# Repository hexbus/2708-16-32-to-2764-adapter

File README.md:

# 2708 / 2716 / 2732 to 2764 adapter

A **28 × 38.5 mm** read-only adapter for Intel-pinout 2708, 2716 and 2732 sockets. It takes a 5 V DIP-28 2764/27C64 EPROM or Microchip AT28C64B EEPROM. The three host shunts sit beside the memory and remain accessible with it installed. The notched top outline marks all 28 memory pads.

Program the replacement chip separately. Place the original image at offset **0x0000** in the 8 KiB image for the replacement. The rest can be filled with `FF`.

Check the host's +5 V current budget, especially in a 2708 socket. The Intel 2708 datasheet specifies up to 10 mA from +5 V. An Intel NMOS 2764 can draw up to 105 mA from that rail with VPP tied to VCC. Allow for the replacement's specified read current and the adapter's pull-up. [Intel 2708 DC characteristics](https://deramp.com/downloads/mfe_archive/050-Component%20Specifications/Intel/Memory%20Components/Intel%202708.pdf) · [Intel 2764 DC characteristics](https://deramp.com/downloads/mfe_archive/050-Component%20Specifications/Intel/Memory%20Components/Intel%202764.pdf)

| Host socket | JP1 CE | JP2 A10 | JP3 A11 | Bytes visible |
| --- | --- | --- | --- | --- |
| 2708 | 1–2 | 1–2 | 1–2 | `0000–03FF` (1 KiB) |
| 2716 | 2–3 | 2–3 | 1–2 | `0000–07FF` (2 KiB) |
| 2732 / 2732A | 2–3 | 2–3 | 2–3 | `0000–0FFF` (4 KiB) |

On the top, with the EPROM notch up, the shunts are labeled CE, A10 and A11 from top to bottom. The square pad on each is pin 1, nearest the notch end. Use one shunt per header. Set the shunts with power off and verify the host socket pinout before inserting the adapter. The three-supply TI TMS2716 and the TMS2532 have different pinouts.

Each host shunt header has its own outline on the top. Read the underside chart with its notch marker up. **↑** means place the shunt toward the notch (pins 1–2). **↓** means place it away from the notch (pins 2–3).

Bridge **JP4** for a 2764/27C64 that requires +5 V on VPP during reads. Leave it open for the AT28C64B, which has NC on pin 1. The socket is for normal reads only. Programming voltages on the host's control pins are outside the design limits.

## Wiring

| Signal | 24-pin host J1 | 28-pin memory U1 |
| --- | --- | --- |
| A7 through A0 | 1–8 | 3–10 |
| D0 through D2 | 9–11 | 11–13 |
| GND | 12 | 14 and A12 on pin 2 |
| D3 through D7 | 13–17 | 15–19 |
| /CE | 20 in 2708 mode, 18 otherwise | 20, with a 10 kΩ pull-up |
| A10 | GND in 2708 mode, 19 otherwise | 21, through R1 |
| /OE | 20 in all modes | 22 |
| A11 | 21 in 2732 mode, GND otherwise | 23, through R2 |
| A9 and A8 | 22 and 23 | 24 and 25 |
| +5 V | 24 | 28 and pin 27 (/PGM or /WE) |
| VPP | JP4, from +5 V | 1 |
| NC | — | 26 |

In 2708 mode, host pin 20 controls both /CE and /OE. When the host pulls that pin low, the replacement drives the data bus. When the pin goes high, the replacement releases the bus. A10, A11 and A12 are held low, so the host's ten address lines select the first 1 KiB.

The 2708 shunt settings isolate host pins 18, 19 (+12 V) and 21 (−5 V) from the memory. R1 with D1/D2 clamps A10. R2 with D3/D4 clamps A11. The resistors limit current if a misplaced shunt connects an address input to one of those rails while the adapter is powered. Set the correct host mode for the enable signals as well.

R1–R3 are upright DIN0204 resistors. D1–D4 are upright BAT85 Schottky diodes. On each diode, put the banded cathode lead in the rounded square pad inside the printed circle. C1 is a low-profile 0805 under the memory footprint. [Vishay MRS16 dimensions](https://www.vishay.com/docs/28724/mrs16m25.pdf) · [Philips BAT85 datasheet](https://media.digikey.com/pdf/Data%20Sheets/Philips%20Semiconductor%20PDFs/BAT85.pdf)

## Files and fabrication

- **[Download the Gerber ZIP — Rev B with through-hole diodes](https://github.com/hexbus/2708-16-32-to-2764-adapter/raw/refs/heads/main/gerbers/2708-16-32-to-2764-adapter-rev-b-through-hole.zip)**
- **[Order at JLCPCB using my referral link](https://jlcpcb.com/?from=RVDYTTLKZHK)**
- [KiCad project](hardware/2708-16-32-to-2764-adapter.kicad_pro), [schematic](hardware/2708-16-32-to-2764-adapter.kicad_sch) and [BOM](hardware/bom.csv)
- Original adapter layout and credit carried forward from [hexbus/2364-adapter](https://github.com/hexbus/2364-adapter). See [LICENSE](LICENSE).

Download the Gerber ZIP, open JLCPCB through the referral link, and upload
the ZIP manually. Select **2 layers, 1.6 mm FR4 and 1 oz copper**, and confirm
the detected board size is **28 × 38.5 mm** before ordering. I may receive
referral rewards for qualifying new users.

| Top | Bottom, viewed from underneath |
| --- | --- |
|  |  |

The exact ZIP was checked for copper connectivity, all three shunt settings, the 28 × 38.5 mm outline, plated drill sizes and locations, all solderable pad openings and silkscreen clearance. The previews come from the ZIP. Physical fit, soldering, bus timing and operation still need a prototype test.

For a first test, check socket fit, diode polarity and +5 V at U1 pin 28 before installing the memory. With a known image programmed at offset zero, read back the full 1 KiB, 2 KiB or 4 KiB window in the matching host mode. Record the host, EPROM part number and mode tested.

Host datasheets for the [Intel 2708](https://deramp.com/downloads/mfe_archive/050-Component%20Specifications/Intel/Memory%20Components/Intel%202708.pdf), [Intel 2716](https://deramp.com/downloads/mfe_archive/050-Component%20Specifications/Intel/Memory%20Components/Intel%202716.pdf) and [Intel 2732](https://deramp.com/downloads/mfe_archive/050-Component%20Specifications/Intel/Memory%20Components/Intel%202732.pdf).

Replacement memory datasheets for the [Intel 2764](https://deramp.com/downloads/mfe_archive/050-Component%20Specifications/Intel/Memory%20Components/Intel%202764.pdf), [ST M27C64A](https://media.digikey.com/pdf/Data%20Sheets/ST%20Microelectronics%20PDFS/m27c64a_Rev2006.pdf) and [Microchip AT28C64B](https://ww1.microchip.com/downloads/en/DeviceDoc/doc0270.pdf).

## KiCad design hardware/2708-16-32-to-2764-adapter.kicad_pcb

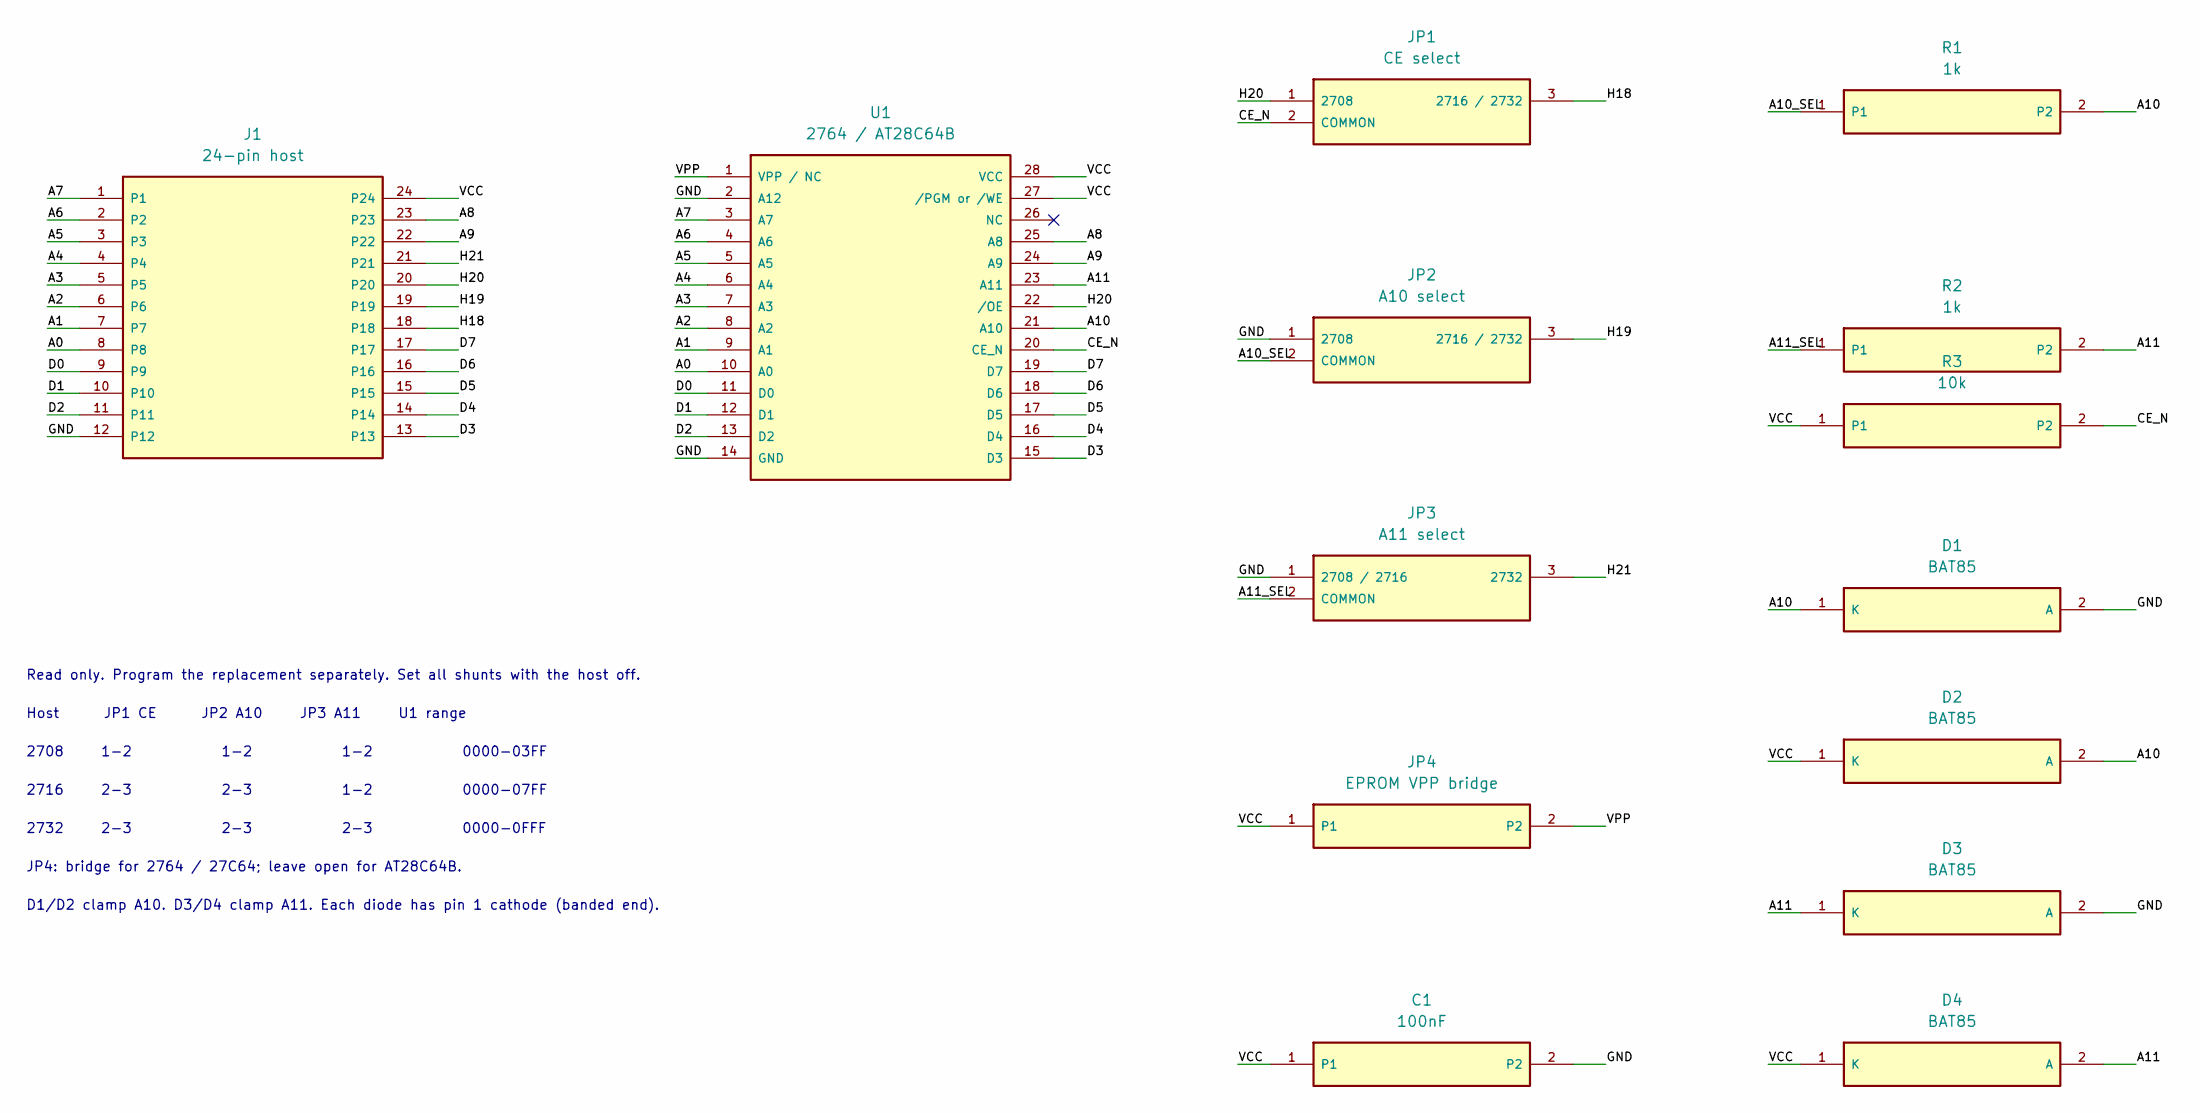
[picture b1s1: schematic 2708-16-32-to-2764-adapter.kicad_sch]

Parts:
C1: 100nF; C_0805
D1, D2, D3, D4: BAT85; BAT85_Upright
J1: 24-pin host; DIP24_Male_15.24mm
JP1: CE select; Shunt_1x03
JP2: A10 select; Shunt_1x03
JP3: A11 select; Shunt_1x03
JP4: EPROM VPP bridge; SolderJumper_Open
R1, R2: 1k; R_Axial_DIN0204_L3.6mm_D1.6mm_P2.54mm_Vertical
R3: 10k; R_Axial_DIN0204_L3.6mm_D1.6mm_P2.54mm_Vertical
U1: 2764 / AT28C64B; DIP28_SocketStrips_15.24mm

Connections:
/A0: J1.8, U1.10 (A0)
/A1: J1.7, U1.9 (A1)
/A2: J1.6, U1.8 (A2)
/A3: J1.5, U1.7 (A3)
/A4: J1.4, U1.6 (A4)
/A5: J1.3, U1.5 (A5)
/A6: J1.2, U1.4 (A6)
/A7: J1.1, U1.3 (A7)
/A8: J1.23, U1.25 (A8)
/A9: J1.22, U1.24 (A9)
/A10: D1.1 (K), D2.2 (A), R1.2, U1.21 (A10)
/A10_SEL: JP2.2 (COMMON), R1.1
/A11: D3.1 (K), D4.2 (A), R2.2, U1.23 (A11)
/A11_SEL: JP3.2 (COMMON), R2.1
/CE_N: JP1.2 (COMMON), R3.2, U1.20 (CE_N)
/D0: J1.9, U1.11 (D0)
/D1: J1.10, U1.12 (D1)
/D2: J1.11, U1.13 (D2)
/D3: J1.13, U1.15 (D3)
/D4: J1.14, U1.16 (D4)
/D5: J1.15, U1.17 (D5)
/D6: J1.16, U1.18 (D6)
/D7: J1.17, U1.19 (D7)
/GND: C1.2, D1.2 (A), D3.2 (A), J1.12, JP2.1 (2708), JP3.1 (2708 / 2716), U1.2 (A12), U1.14 (GND)
/H18: J1.18, JP1.3 (2716 / 2732)
/H19: J1.19, JP2.3 (2716 / 2732)
/H20: J1.20, JP1.1 (2708), U1.22 (/OE)
/H21: J1.21, JP3.3 (2732)
/VCC: C1.1, D2.1 (K), D4.1 (K), J1.24, JP4.1, R3.1, U1.27 (/PGM or /WE), U1.28 (VCC)
/VPP: JP4.2, U1.1 (VPP / NC)

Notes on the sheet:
Read only. Program the replacement separately. Set all shunts with the host off.
Host JP1 CE JP2 A10 JP3 A11 U1 range
2708 1-2 1-2 1-2 0000-03FF
2716 2-3 2-3 1-2 0000-07FF
2732 2-3 2-3 2-3 0000-0FFF
JP4: bridge for 2764 / 27C64; leave open for AT28C64B.
D1/D2 clamp A10. D3/D4 clamp A11. Each diode has pin 1 cathode (banded end).

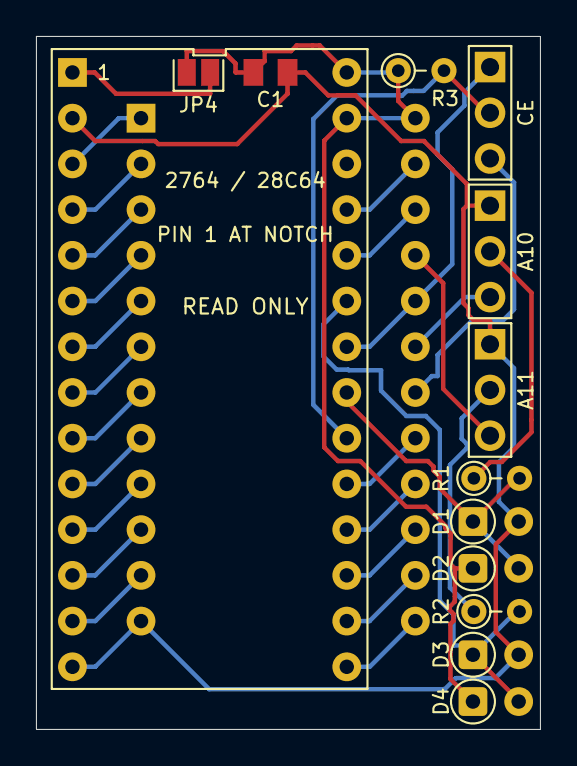
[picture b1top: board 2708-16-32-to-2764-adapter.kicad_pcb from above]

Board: 2 copper layers, 28.0 x 38.5 mm, 14 parts (1 on the bottom side), 30 nets.

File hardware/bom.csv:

Reference,Quantity,Description,Specification
PCB,1,Rev B adapter PCB,28 x 38.5 mm two-layer FR4
U1 socket,2,Turned-pin female socket strips,1x14 at 2.54 mm pitch with 15.24 mm row spacing and 0.8 mm PCB holes
J1 plug,2,Round-pin male adapter strips,1x12 at 2.54 mm pitch with 15.24 mm row spacing and 0.8 mm PCB holes
JP1–JP3,3,Vertical male pin headers,1x3 at 2.54 mm pitch with 1.0 mm PCB holes
Shunts,3,Removable shorting shunts,2.54 mm pitch
JP4,0,Solder bridge,Close for 2764 or 27C64 and leave open for AT28C64B
C1,1,100 nF ceramic capacitor,Low-profile 0805 X7R or X5R at least 16 V
R1 R2,2,1 kΩ axial resistor,DIN0204 upright with 2.54 mm lead spacing and 0.7 mm PCB holes; at least 0.125 W
R3,1,10 kΩ axial resistor,DIN0204 upright with 2.54 mm lead spacing and 0.7 mm PCB holes
D1–D4,4,BAT85 Schottky diode,Upright DO-35 with 2.54 mm lead spacing and 0.8 mm PCB holes; banded lead at pad 1
U1,1,Programmed read-only memory,5 V DIP28 2764 or 27C64 or AT28C64B

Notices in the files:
hardware/2708-16-32-to-2764-adapter.kicad_pcb:
(c) 2026 REV B
